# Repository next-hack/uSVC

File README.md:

# uSVC
uChip Simple VGA Console
An open source, easy to build retro game console!

This project is a very simple VGA console, based on uChip. Games are loaded from the SD card, and you can use standard keyboards or gamepads.

The console is made of few, easy to find and easy to solder components. There is only one SMD component: the micro-SD card reader.

The ATSAMD21 (A 48 MHz Cortex M0+) generates the VGA and audio signals, and provides up to 256 simultaneous colors. There are 3 video modes:
- Bitmapped Mode
- 8 bpp tiled mode
- 4 bpp tiled mode.

Each mode has its own peculiarity. For more information, visit next-hack.com!

You might also want to take a look at:

- The game editor source code: https://github.com/next-hack/uChipGameMapEditor
- Redballs, a Worms-like game: https://github.com/next-hack/uSVC_Redballs
- Fairplay race: https://github.com/next-hack/uSVC_Fairplay-race
- uSVC Tetris: https://github.com/next-hack/uSVC_Tetris

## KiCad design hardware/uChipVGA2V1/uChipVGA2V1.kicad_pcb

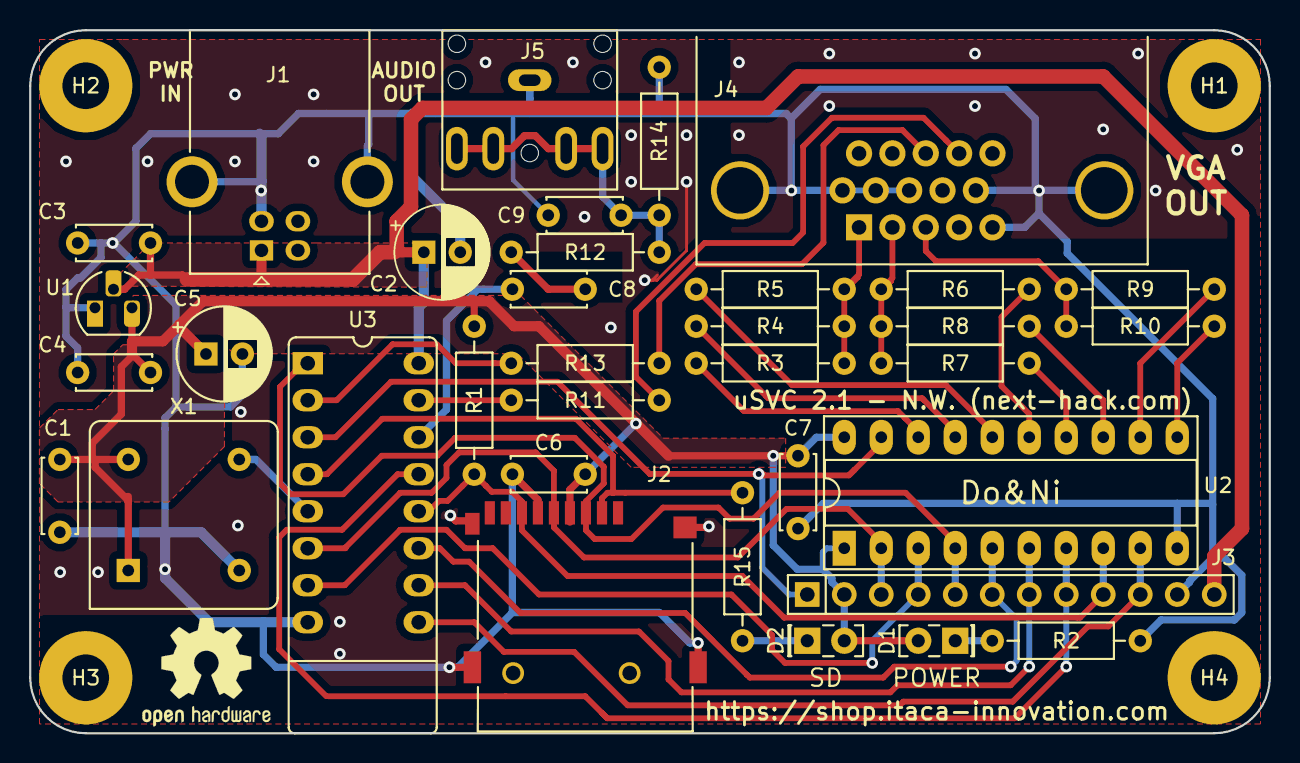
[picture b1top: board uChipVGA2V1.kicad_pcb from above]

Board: 2 copper layers, 85.1 x 48.3 mm, 40 parts (0 on the bottom side), 34 nets.

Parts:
C1, C3, C4, C6, C7, C8: 1u; C_Disc_D5.0mm_W2.5mm_P5.00mm
C2, C5: 100u; CP_Radial_D6.3mm_P2.50mm
C9: 22n; C_Disc_D5.0mm_W2.5mm_P5.00mm
D1, D2: LED; LED_Rectangular_W5.0mm_H2.0mm
H1, H2, H3, H4: MountingHole; MountingHole_3.2mm_M3_Pad
J1: USB_B; USB_B_OST_USB-B1HSxx_Horizontal
J2: Micro_SD_CardDet; HYC77TF09200
J3: Conn_01x12; PinHeader_1x12_P2.54mm_Vertical
J4: DB15_Female_HighDensity_MountingHoles; DSUB-15-HD_Female_Horizontal_P2.29x2.54mm_EdgePinOffset8.55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
J5: JACKAUDIO35; SJ-3525NG
LOGO1: Logo_Open_Hardware_Large; OSHW-Logo2_9.8x8mm_SilkScreen
R1, R14: 10k; R_Axial_DIN0207_L6.3mm_D2.5mm_P10.16mm_Horizontal
R2, R9, R15: 390; R_Axial_DIN0207_L6.3mm_D2.5mm_P10.16mm_Horizontal
R3, R6: 470; R_Axial_DIN0207_L6.3mm_D2.5mm_P10.16mm_Horizontal
R4, R7, R12: 1k; R_Axial_DIN0207_L6.3mm_D2.5mm_P10.16mm_Horizontal
R5, R8: 2k2; R_Axial_DIN0207_L6.3mm_D2.5mm_P10.16mm_Horizontal
R10: 820; R_Axial_DIN0207_L6.3mm_D2.5mm_P10.16mm_Horizontal
R11, R13: 22; R_Axial_DIN0207_L6.3mm_D2.5mm_P10.16mm_Horizontal
U1: MCP1700-3302E-TO; TO-92L_HandSolder
U2: 74AHC245; DIP-20_W7.62mm_Socket_LongPads
U3: uChip1V5_LargePads
X1: CXO_DIP8; Oscillator_DIP-8

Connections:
+3V3: C1.1, C4.1, C5.1, C6.1, C7.1, D1.2, D2.2, J2.4, J3.2, R1.2, U1.3, U2.1, U2.20, X1.1, X1.8
+5V: C2.1, C3.1, J1.1, J3.12, U1.2, U3.16
/B: J4.3, R9.1, R10.1
/B0: J3.10, U2.9, U3.9
/B1: J2.7, J3.9, R1.1, U2.8, U3.12
/DISABLE: J3.1, U2.19, U3.3
/G: J4.2, R6.1, R7.1, R8.1
/G0: J3.8, U2.7, U3.13
/G1: J3.7, U2.6, U3.10
/G2: J3.6, U2.5, U3.11
/HSYNC: R13.2, U3.2
/R: J4.1, R3.1, R4.1, R5.1
/R0: J2.3, J3.5, U2.4, U3.1
/R1: J3.4, U2.3, U3.7
/R2: J2.5, J3.3, U2.2, U3.6
/SDCS: J2.2, R15.1, U3.4
/VDAC: C8.2, U3.14
/VSYNC: R11.2, U3.15
/bB0: R10.2, U2.11
/bB1: R9.2, U2.12
/bG0: R8.2, U2.13
/bG1: R7.2, U2.14
/bG2: R6.2, U2.15
/bR0: R5.2, U2.16
/bR1: R4.2, U2.17
/bR2: R3.2, U2.18
GND: C1.2, C2.2, C3.2, C4.2, C5.2, C6.2, C7.2, C9.1, J1.4, J1.5, J2.6, J2.MP1, J2.MP2, J2.MP3, J2.MP4, J3.11, J4.0, J4.5, J4.6, J4.7, J4.8, J4.10, J5.1, R2.1, R14.1, U1.1, U2.10, U3.8, X1.4
unnamed: C8.1, R12.2
unnamed: C9.2, J5.2, J5.3, J5.4, J5.5, R12.1, R14.2
unnamed: D1.1, R2.2
unnamed: D2.1, R15.2
unnamed: J4.13, R13.1
unnamed: J4.14, R11.1
unnamed: U3.5, X1.5

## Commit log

2020-06-18 Added schematics in pdf format
2020-06-18 updated fine print.
2020-10-28 Added uSVC Template Project
    Added uSVC Template Project for Atmel Studio 7
2020-11-22 Added freeSpriteTiles() API
    Added freeSpriteTiles() API to be called (instead of restoreBackgroundTiles()) when no background need to be restored (e.g. when rewriting the whole vram)
2020-11-22 Improved USB power handling
    Improved USB power handling technique
2020-12-08 Fixed Audio Engine Bug, added game loader and demos
    Fixed a bug for which a channel used for sound fx could not be used anymore for a regular note, for patchless fx.
    Added demos, ad game loader.
2020-12-08 Updated readme with links to game repos.
2020-12-12 triggerFx now can detune sample and force channel usage.
2020-12-12 removed unnecessary lines.
2021-02-20 Fixed bug on setSongSpeed()
2021-02-20 Fixed setSongSpeed() bug on all projects
2021-02-21 Added game and demo packages
